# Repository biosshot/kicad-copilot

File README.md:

# KiCad Copilot

AI-powered MCP server for KiCad. Create and modify schematics from natural language, search real components, work with hierarchical projects, generate PCB placement, route boards locally, and create simple copper pours directly through an AI agent.

KiCad Copilot is the KiCad counterpart to [EasyEDA Copilot](https://github.com/biosshot/easyeda-copilot). It provides the same core circuit-generation and PCB automation capabilities—and goes further with file-oriented hierarchical projects, recoverable checkpoints, native `kicad-cli` integration, and fully local PCB routing.

> **Integrated analysis:** KiCad Copilot downloads a pinned, verified [kicad-happy](https://github.com/aklofas/kicad-happy) v2.2.0 release on first use of `analyze_schematic` or `analyze_pcb`. The MCP tools return compact, token-efficient actionable findings and focused design data.

<p align="center">

</p>

## What it does

KiCad Copilot gives AI agents a high-level, file-oriented interface to KiCad:

- **Generate and modify schematics**: add, remove, replace, and connect real components without editing every KiCad object individually.
- **Rebuild schematic blocks**: reorganize selected components while preserving their electrical connections.
- **Search components and reusable blocks**: resolve components by MPN or part UUID and insert proven functional circuits.
- **Work with KiCad projects**: inspect project trees and create projects, standalone schematics, hierarchical sheets, and PCB files.
- **Preserve recoverable checkpoints**: save, list, and restore exact versions of individual KiCad files.
- **Synchronize schematic and PCB**: explicitly import schematic changes into the associated board.
- **Generate PCB placement**: describe board constraints in a compact JavaScript DSL, checkpoint and apply returned layouts, and validate changed mechanics with native KiCad views.
- **Route locally**: use `eda-copilot-router` with its managed KRT backend without sending routing work to an external service.
- **Create copper pours**: add simple full-board zones with optional stitching vias.
- **Use native KiCad tooling**: discover `kicad-cli` for ERC, DRC, previews, exports, manufacturing files, and other native operations.

KiCad Copilot works directly with saved `.kicad_pro`, `.kicad_sch`, and `.kicad_pcb` files. It does not require KiCad IPC or a plugin installed inside KiCad.

## Examples

These projects were generated and iterated through KiCad Copilot. The complete KiCad source files are available in the [`examples`](examples) directory.

### ATmega328P development board

A hierarchical ATmega328P design with the MCU core, clock, reset, decoupling, USB-UART power, Nano-compatible headers, and debug connections split across functional sheets.

<table>
  <tr>
    <td align="center" width="50%"><br><sub>Project overview</sub></td>
    <td align="center" width="50%"><br><sub>USB-UART and power</sub></td>
  </tr>
  <tr>
    <td align="center" width="50%"><br><sub>MCU core</sub></td>
    <td align="center" width="50%"><br><sub>Nano headers and debug</sub></td>
  </tr>
</table>

[Download the ATmega328P project](examples/atmega328p_dev.zip)

### Geiger high-voltage supply

A larger multi-sheet design covering power input, 3.3 V regulation, the high-voltage generator, flyback stage, feedback, detector, controller, and user interface.

<table>
  <tr>
    <td align="center" width="50%"><br><sub>Project overview</sub></td>
    <td align="center" width="50%"><br><sub>Power input</sub></td>
  </tr>
  <tr>
    <td align="center" width="50%"><br><sub>High-voltage generator</sub></td>
    <td align="center" width="50%"><br><sub>Detector</sub></td>
  </tr>
  <tr>
    <td align="center" width="50%"><br><sub>Controller UI</sub></td>
    <td align="center" width="50%"><br><sub>3.3 V power</sub></td>
  </tr>
  <tr>
    <td align="center" width="50%"><br><sub>HV flyback</sub></td>
    <td align="center" width="50%"><br><sub>HV feedback</sub></td>
  </tr>
  <tr>
    <td align="center" colspan="2"><br><sub>User interface</sub></td>
  </tr>
</table>

[Download the Geiger high-voltage project](examples/geiger_hv.zip)

### RP2350 development board

A hierarchical RP2350 design with power, clock, flash, USB/debug, GPIO headers, and an AI-generated PCB placement. The example includes the placement DSL and an editable KiCad board.

<table>
  <tr>
    <td align="center" width="50%"><br><sub>Project overview</sub></td>
    <td align="center" width="50%"><br><sub>Power</sub></td>
  </tr>
  <tr>
    <td align="center" width="50%"><br><sub>RP2350 and clock</sub></td>
    <td align="center" width="50%"><br><sub>Flash</sub></td>
  </tr>
  <tr>
    <td align="center" width="50%"><br><sub>USB and debug</sub></td>
    <td align="center" width="50%"><br><sub>GPIO headers</sub></td>
  </tr>
</table>

<p align="center">
  
  <br><sub>KiCad 3D render of the generated PCB placement</sub>
</p>

[Download the RP2350 project](examples/rp2350_debug.zip)

## Installation

Add the MCP server to your AI agent.

Codex:

```bash
codex mcp add kicad-copilot -- npx -y kicad-copilot-mcp
```

Claude Code:

```bash
claude mcp add kicad-copilot -- npx -y kicad-copilot-mcp
```

Generic MCP configuration:

```json
{
  "mcpServers": {
    "kicad-copilot": {
      "command": "npx",
      "args": ["-y", "kicad-copilot-mcp"]
    }
  }
}
```

Restart the MCP client after adding the server. KiCad Copilot includes local workflow documentation for the agent; tool descriptions expose its installed path automatically.

## Requirements

- Node.js 20.19 or newer
- KiCad 9 or 10
- Python 3 for managed EasyEDA2KiCad installation and kicad-happy analysis

KiCad Copilot searches for `kicad-cli` in `PATH` and standard KiCad installation locations, preferring KiCad 10 when multiple supported versions are installed. Set `KICAD_CLI_PATH` when the executable is stored elsewhere.

The first real-component conversion uses an existing EasyEDA2KiCad installation or installs it automatically into a managed local virtual environment.

The first design-analysis call downloads the pinned kicad-happy release into the shared
EDA Copilot asset cache after verifying its archive size and SHA-256 hash. Set
`KICAD_HAPPY_DIR` to use a trusted local checkout instead.

### Local backend and standalone skill

Schematic layout, component search, PCB sizes and placement call `eda-copilot-backend`
directly. No Copilot HTTP server, server URL or server credentials are needed.
Catalog search and first-use downloads still require network access. KiCad supplies
its symbol and footprint geometry as UUID-keyed fallback maps; catalog geometry wins
when it resolves successfully.

The npm package pins `eda-copilot-backend@0.5.1`. Download
`kicad-copilot-skill.zip` from [GitHub Releases](https://github.com/biosshot/kicad-copilot/releases/latest)
and follow the [installation guide](docs/install-guide.md).

From source, run `npm ci` and `npm run build:skill` for the portable skill, or
`npm run build:skill:bundled` to include dependencies for the current platform.
`npm run check:skill` validates the generated `skill/`.

Use `export_pcb_routing_board` for a saved Board V2 snapshot and
`run_pcb_analysis` for local DSL calculations and JSON/PNG reports. See the
[PCB analysis skill](docs/pcb-analysis/SKILL.md).

Development checks: `npm run check` runs types, build and fast regression tests.
`npm run test:native` runs native KiCad acceptance; `npm run test:local-backend` checks
the actual local placement backend. Set `KICAD_CLI_PATH` for nonstandard installations.

## Schematic workflow

Ask the agent to inspect a KiCad project or give it the path to a target `.kicad_sch` file. A typical request can be as simple as:

```text
Open D:\Projects\sensor\sensor.kicad_pro and add a 3.3 V regulator block to the Power sheet.
```

The agent can inspect the project tree, read the target sheet as compact component/net JSON, find exact components, assemble the requested change, and validate the saved result through KiCad.

Hierarchical projects remain file-oriented: each physical schematic sheet is modified through its own `.kicad_sch` path, while project-wide context is used where the operation requires the complete signal map.

### File synchronization

KiCad Copilot changes files on disk. KiCad does not reliably merge those changes with newer unsaved edits in an already open editor.

Before a write:

1. Save intentional changes in KiCad.
2. Avoid keeping the only copy of newer work in the editor buffer.

After a write:

1. Reload, revert, or reopen the document in KiCad.
2. Do not overwrite the updated file with an older editor buffer.

## PCB workflow

PCB placement, mechanics, copper, and routing can be requested independently. For a complete board:

1. Synchronize the target `.kicad_pcb` only when the schematic changed.
2. Select new, preserved-outline, add-only, or subset placement.
3. Validate connectors and other changed mechanics first.
4. Complete and analyze placement.
5. Apply only the requested stackup, rules, copper, and routing operations.
6. Run focused PCB analysis and final native KiCad DRC.

Every placement response containing a PCB is checkpointed and applied atomically, including preview and issue-bearing results; no separate assembly call exists. Solver PNG/SVG output is diagnostic. When mechanics change, the agent validates the applied board through focused analysis and a native `kicad-cli` render, then asks whether to keep, fix, or restore the result.

Placement and router DSL execution remain separate operations. This keeps schematic-to-PCB synchronization explicit and makes it possible to clear or rebuild routing without deleting placed components.

## KiCad CLI

`get_project_info` reports the discovered `kicad-cli` path and version. Agents should use the native CLI whenever KiCad already provides the operation, including:

- schematic ERC and PCB DRC;
- schematic and PCB PDF/SVG exports;
- 3D PCB renders;
- Gerber and drill generation;
- BOM, position, STEP, STL, GLB, and VRML exports;
- project jobsets and format upgrades.

See [KiCad CLI workflow](docs/kicad-cli.md) for ready-to-use commands.

## Design analysis

`analyze_schematic` runs the offline schematic checks and can return focused top-level
overview, hierarchy, block, connectivity, power, bus, BOM, assembly, and verification data.
`analyze_pcb` automatically enriches PCB analysis from the associated schematic, runs
cross-domain checks, and optionally adds thermal, EMC, or trace-proximity analysis. Individual
boolean flags control each optional report field; compact findings are enabled by default.
Long-running PCB layout, PCB routing, and lifecycle audits return a prefixed
`operation_id` such as `pcb-dsl:1a2b3c4d`. Continue any of them with
`wait_operation`; stop obsolete work with `cancel_operation`.
The tools omit internal rule identifiers, runtime metrics, and coordinate-level copper from
the LLM response.

See [design analysis](docs/analysis.md) for the exact compact result contract and workflow.

## Compatibility

| KiCad version | Status    |
| ------------- | --------- |
| KiCad 10      | Supported |
| KiCad 9       | Supported |

Other major versions are rejected because their file formats and CLI behavior are not covered by the current implementation.

## Documentation

- [AI agent instructions](docs/SKILL.md)
- [Full and independent workflows](docs/workflow.md)
- [Schematic workflow](docs/schematic/workflow.md)
- [Circuit modification schema](docs/schematic/circuit-mod.md)
- [Projects and hierarchical sheets](docs/schematic/project-and-sheets.md)
- [Checkpoints](docs/schematic/checkpoints.md)
- [PCB placement workflow and rules](docs/pcb-layout/instructions.md)
- [Mechanical validation](docs/pcb-layout/mechanical-validation.md)
- [Placement DSL](docs/pcb-layout/dsl.ts)
- [PCB routing workflow](docs/pcb-routing/instructions.md)
- [Routing DSL](docs/pcb-routing/dsl.d.ts)
- [KiCad CLI](docs/kicad-cli.md)
- [Design analysis](docs/analysis.md)
- [Verification gates](docs/verification.md)
- [Troubleshooting](docs/troubleshooting.md)

## Development

Call the actual MCP tools from a terminal after `npm run build`:

```sh
node dist/cli.js list
node dist/cli.js call get_schematic @request.json
node dist/cli.js batch @calls.json
```

`request.json` contains the tool arguments, for example `{ "path": "D:/board/main.kicad_sch" }`.
`calls.json` contains an array of `{ "name": "get_schematic", "arguments": { "path": "..." } }` requests.
Use `-` instead of `@file.json` to read JSON from stdin. A batch uses one stdio MCP session and stops on the first error. Results are MCP JSON; tool errors produce exit code 1. Installed packages expose the same commands as `kicad-copilot-cli`.

Run `npm run test:mcp-ldo` to reproduce creation and beautification of two reusable AP2112 LDO sheets connected to three catalogue headers. It uses the local backend and native KiCad CLI, saves requests and results under `.test-output/mcp-ldo`, and verifies local sheet lookup after an MCP restart.

```bash
git clone https://github.com/biosshot/kicad-copilot.git
cd kicad-copilot
npm install
npm run check
npm start
```

Run the MCP Inspector with:

```bash
npm run inspect
```

The repository also contains focused schematic, PCB, and routing test scripts for development against disposable files.

## License

MIT

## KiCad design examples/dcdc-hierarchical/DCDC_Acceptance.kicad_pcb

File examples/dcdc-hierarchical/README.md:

# Hierarchical three-rail DC-DC test board

This is a complete KiCad 10 schematic and routed PCB for a self-contained test project: one 12 V input feeds three independent TPS62130 adjustable buck channels, with separate 3 V A, 3 V B, and 5 V output connectors.

## Open the project

Open `DCDC_Acceptance.kicad_pro` in KiCad 10. The project includes its symbol library, footprint library, and 3D model files under project-relative paths. No external library download is required.

## Schematic hierarchy

```text
DCDC_Acceptance
└── PowerSubsystem
    ├── Buck3V     → 3V_A
    ├── SH2         → 3V_B (second instance of Buck3V.kicad_sch)
    └── Buck5V     → 5V_OUT
```

The PowerSubsystem sheet also contains CN1 (12 V input), CN2 (3V_A), CN3 (3V_B), and CN4 (5V_OUT). Every connector has a separate GND contact. Both 3 V rails use the same child-sheet design with distinct physical references and independent passives. `previews/schematic/` contains rendered sheets, including the two repeated Buck3V instances.

## Electrical assumptions

- Input: 12 V nominal. Keep the eventual source tolerance below the regulator’s 17 V recommended maximum.
- Test load assumption: 0.30 A on each output independently (3V_A, 3V_B, and 5V_OUT). This is a chosen test operating point, not a guaranteed or measured rating.
- Router current assumptions: 0.30 A per output and 0.50 A on the shared 12 V feed. The 0.50 A input value is a conservative planning assumption; converter efficiency and thermal capacity were not measured.
- Divider values use TI’s nominal equation `VOUT = 0.8 V × (1 + Rtop/Rbottom)`: 274 kΩ / 100 kΩ gives 2.992 V nominal; 523 kΩ / 100 kΩ gives 4.984 V nominal. Reference and resistor tolerances affect actual output limits.
- The TPS62130 power-good pin (PG) is intentionally left unconnected. FSW and DEF are tied low. AVIN, PVIN, and EN use the 12 V input.
- AGND, PGND, and exposed pad 17 are tied to the common ground plane. The exposed pad is soldered.

## Board and routing assumptions

- 80 × 50 mm, two copper layers; all components on the top side.
- Provisional stack used for routing calculations: JLCPCB standard 2-layer FR-4, 1.6 mm board, 1 oz outer copper, Dk 4.5. The routing DSL represents the dielectric as the nominal 1.53 mm remainder after 35 µm top and bottom copper. This is an approximation for current/routing calculations, not a verified fabrication stack. No controlled-impedance requirement or claim is made.
- Ground copper zones are on both outer layers. Native analysis reports 71 vias and one connected ground domain; the router also reported that some local stitching vias could not be placed near QFN ground pads.
- PCB analysis reports 196 routed track segments, 71 vias, two ground zones, and zero unrouted nets. The router’s terminal summary reported 92 logical tracks; the analyzer’s 196 is the final segment count after KiCad geometry is loaded.
- The board is sparse, with converter circuitry grouped toward one side. It was accepted as a functional routing/ hierarchy test fixture, not optimized for area or fabrication release.

## Local JST footprint correction

The local project copy of the JST XH footprint has two numbered 1.8 mm plated pads for the electrical posts and one unnumbered 1.2 mm locating-boss hole. The catalogue geometry marked the unnumbered boss hole as plated copper with a 1.2 mm drill, which created zero-annulus DRC errors. The local `.pretty` footprint and its four board instances were changed to KiCad NPTH using the KiCad 10 `pcbnew` API. The numbered electrical pads remain plated. JST’s XH drawing distinguishes the electrical PCB holes from the molded boss dimensions; see the linked manufacturer catalogue below. This correction is limited to this example project and does not alter the upstream catalogue/importer.

## Verification and remaining findings

- Native KiCad 10 ERC: one error remains: `power_pin_not_driven` on an AGND power-input pin in the repeated Buck3V instance. The external input connector is passive and the available schematic operations do not provide a PWR_FLAG. This is recorded rather than suppressed.
- Native KiCad 10 DRC with zone refill: zero errors and zero unconnected items; 30 warnings remain: 28 library-footprint mismatch warnings and two silkscreen-clearance warnings on C16.
- PCB analysis: the routed connectivity is complete. It also flags missing assembly fiducials and 0/14 test-point coverage. No fiducials or test points were added because this is a functional hierarchy/routing test fixture, not an assembly-release design.
- No regulator load test, output ripple/accuracy measurement, thermal test, EMI test, transient test, or fabrication validation was performed. Check the ceramic capacitors’ effective capacitance under DC bias and review the library-footprint warnings before manufacturing.

The native ERC and DRC JSON, the independent schematic netlist, and routing intent are under `evidence/`. The board preview is under `previews/`.

## Sources

- [TI TPS62130A datasheet, Rev. F](https://www.ti.com/lit/ds/symlink/tps62130a.pdf)
- [Bourns SRP4020TA datasheet](https://www.bourns.com/docs/product-datasheets/srp4020ta.pdf)
- [JST XH connector catalogue](https://www.jst.com/wp-content/uploads/2025/06/eXH.pdf)
- [JLCPCB PCB capabilities](https://jlcpcb.com/capabilities/pcb-capabilities) and [copper-weight guide](https://jlcpcb.com/help/article/jlcpcb-copper-weight)

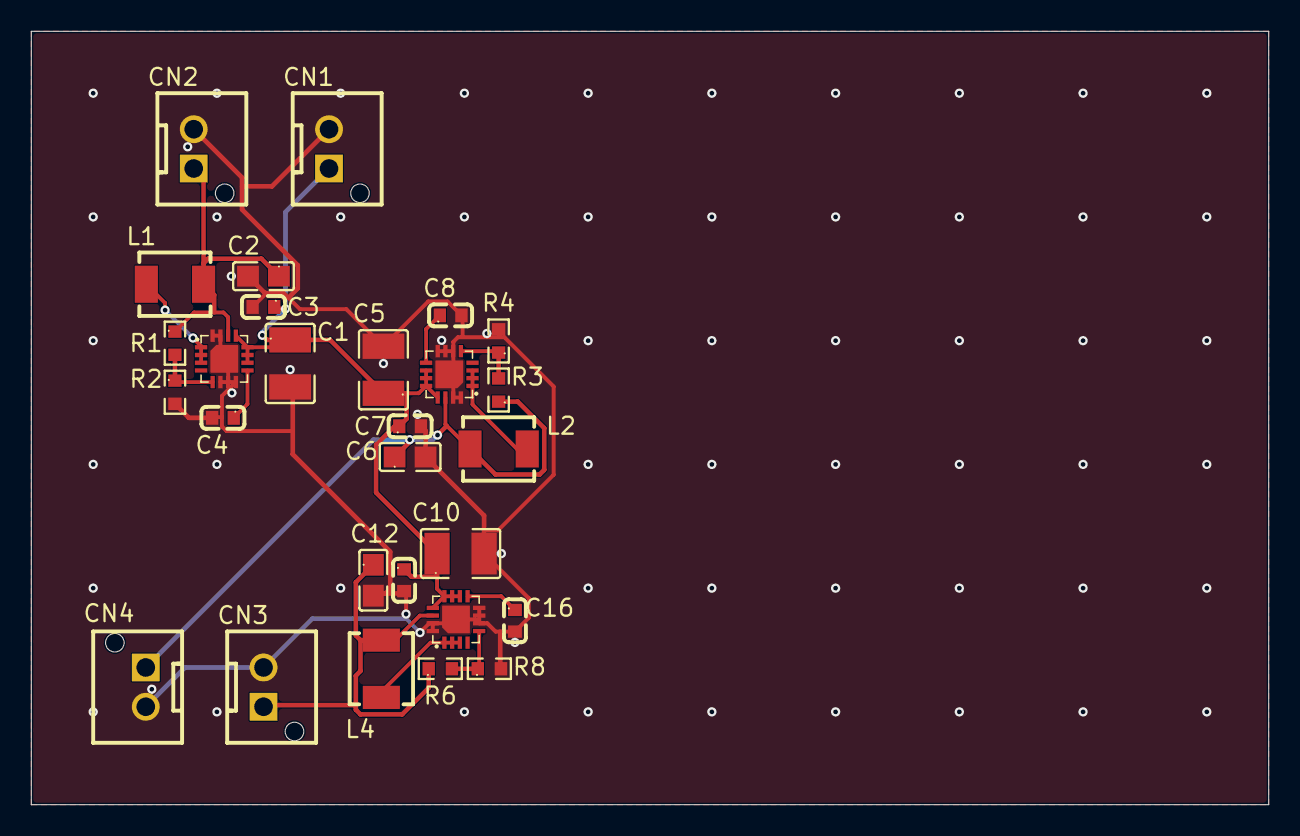
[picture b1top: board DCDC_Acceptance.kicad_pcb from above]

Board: 2 copper layers, 80.0 x 50.0 mm, 28 parts (0 on the bottom side), 14 nets.

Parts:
C1, C5, C10: 10uF; C138687_C1210
C2, C6, C12: 22uF; C45783_C0805
C3, C7, C14: 100nF; C1591_C0603
C4, C8, C16: 3.3nF; C1613_C0603
CN1: 12V_IN; C19267356_CONN-TH_B2B-XH-AM-LF-SN
CN2: 3V_A_OUT; C19267356_CONN-TH_B2B-XH-AM-LF-SN
CN3: 3V_B_OUT; C19267356_CONN-TH_B2B-XH-AM-LF-SN
CN4: 5V_OUT_OUT; C19267356_CONN-TH_B2B-XH-AM-LF-SN
L1, L2, L4: 2.2uH; C719179_IND-SMD_L4.5-W4.1_SRP4020TA
R1, R6: 274k; C482818_R0603
R2, R4, R8: 100k; C14675_R0603
R3: 523k; C185324_R0603
U1, U2, U4: TPS62130ARGTR; C337502_VQFN-16_L3.0-W3.0-P0.50-BL-EP1.7

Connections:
/PowerSubsystem/3V_A: C2.1, CN2.1, L1.2, R1.1, U1.14
/PowerSubsystem/3V_B: C12.1, CN3.1, L4.2, R6.1, U4.14
/PowerSubsystem/5V_OUT: C6.1, CN4.1, L2.2, R3.1, U2.14
/PowerSubsystem/Buck3V/FB: R1.2, R2.1, U1.5
/PowerSubsystem/Buck3V/SS: C4.1, U1.9
/PowerSubsystem/Buck3V/SW: L1.1, U1.1, U1.2, U1.3
/PowerSubsystem/Buck5V/FB: R3.2, R4.1, U2.5
/PowerSubsystem/Buck5V/SS: C8.1, U2.9
/PowerSubsystem/Buck5V/SW: L2.1, U2.1, U2.2, U2.3
/PowerSubsystem/GND: C1.2, C2.2, C3.2, C4.2, C5.2, C6.2, C7.2, C8.2, C10.2, C12.2, C14.2, C16.2, CN1.2, CN2.2, CN3.2, CN4.2, R2.2, R4.2, R8.2, U1.6, U1.7, U1.8, U1.15, U1.16, U1.17, U2.6, U2.7, U2.8, U2.15, U2.16, U2.17, U4.6, U4.7, U4.8, U4.15, U4.16, U4.17
/PowerSubsystem/SH2/FB: R6.2, R8.1, U4.5
/PowerSubsystem/SH2/SS: C16.1, U4.9
/PowerSubsystem/SH2/SW: L4.1, U4.1, U4.2, U4.3
/PowerSubsystem/VIN12: C1.1, C3.1, C5.1, C7.1, C10.1, C14.1, CN1.1, U1.10, U1.11, U1.12, U1.13, U2.10, U2.11, U2.12, U2.13, U4.10, U4.11, U4.12, U4.13
